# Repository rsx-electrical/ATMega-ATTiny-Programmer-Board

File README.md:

# ATMega ATTiny Programmer Board
UofT RSX's ATMega/ATTiny Programmer Board KiCad PCB designs for programming standalone ATMega328[tbd] and ATTiny[tbd] microcontrollers. Uses Arduino as programmer. By programming the microcontroller directly, custom boards can be smaller and cheaper.

## To-do
- 

## Repository Structure 
```
Programmer-Board/
├── ATMega/
│   └── ...
│
├── ATTiny/
│   └── ...
│
├── Programmer Board/
│   └── ...
│
├── guide.txt
└── README.md
```
## History/Patch Notes

### v1.0 - TBD
- Final Design Version 1

### v0.2 - TBD
- 

### v0.1 - Init
- General Project Struct Formed

## Materials
- Arduino Header
- Electrolytic Capacitor 10uF
- Decoupling Capacitors 100nF
- Resistor [1 - 10kΩ]
- ATMega328[tbd] or ATTiny[tbd] Socket

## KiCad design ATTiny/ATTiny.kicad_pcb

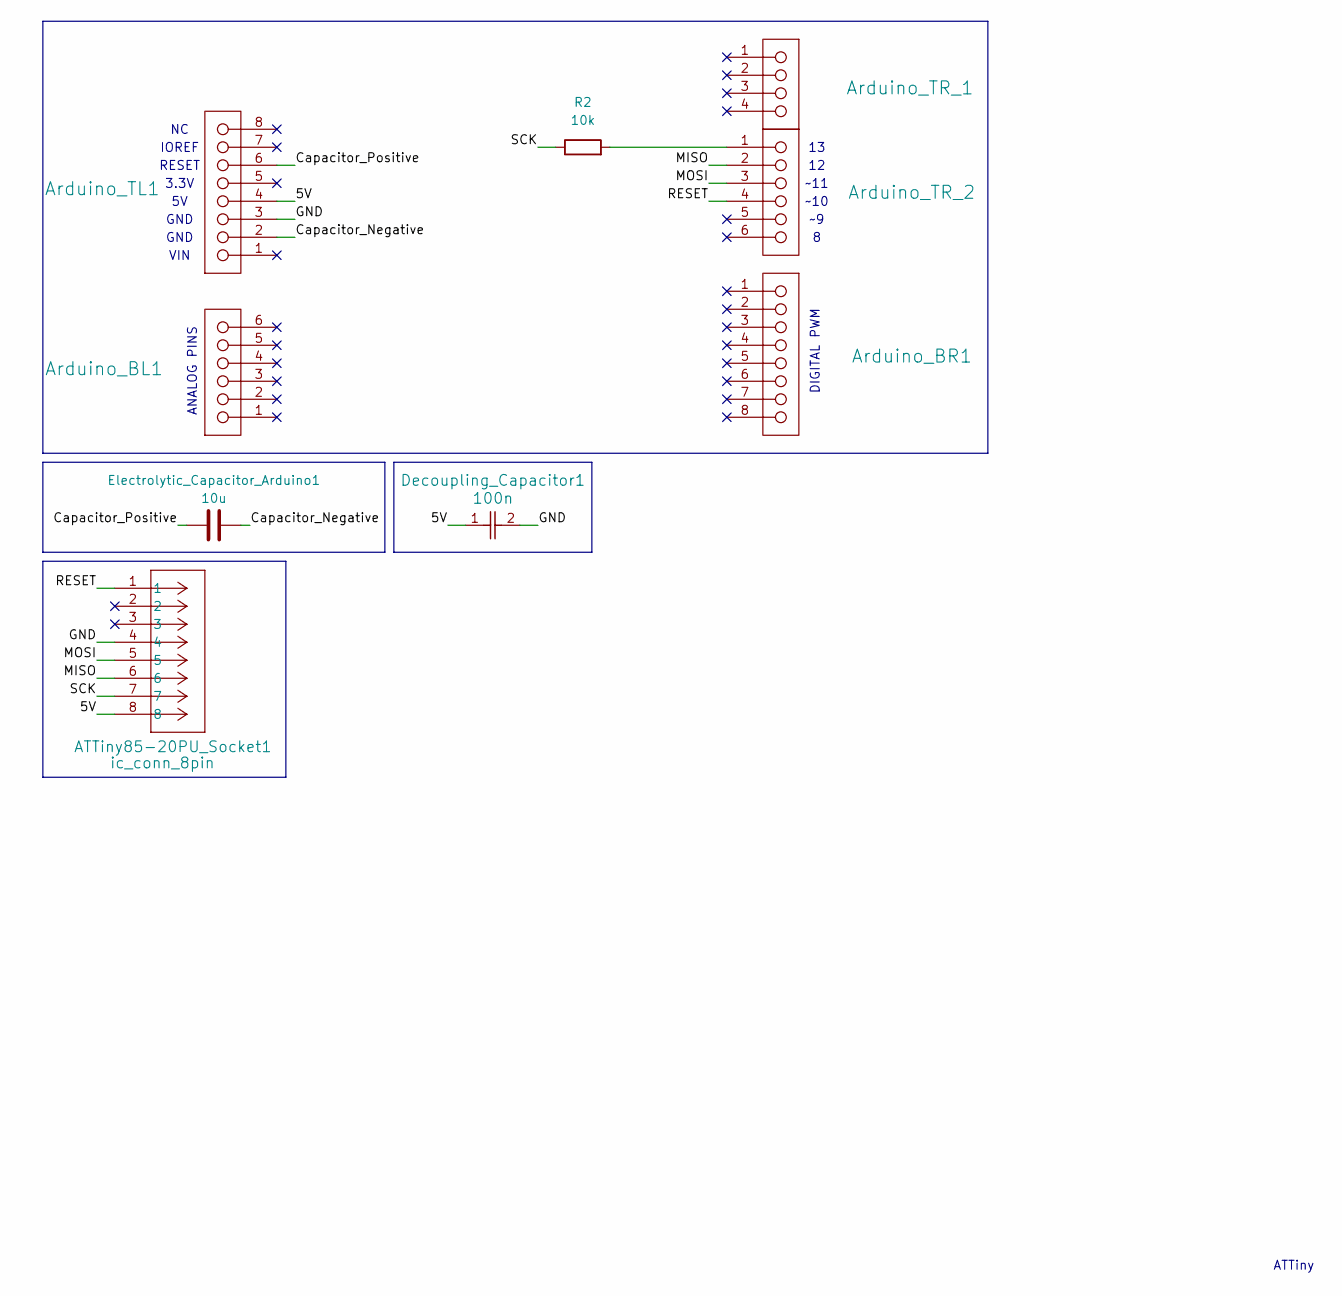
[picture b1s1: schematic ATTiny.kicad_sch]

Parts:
ATTiny85-20PU_Socket1: ic_conn_8pin; CONN8_1-2199298-2_TEC
Arduino_BL1: header_1x6_arduino; PinHeader_1x06_P2.54mm_Vertical; Working Voltage 250V; Withstanding Voltage 500V; Manufacturer Part Number 61000613321
Arduino_BR1: header_1x8_arduino; PinHeader_1x08_P2.54mm_Vertical; Working Voltage 250V; Withstanding Voltage 500V; Manufacturer Part Number 61000813321
Arduino_TL1: header_1x8_arduino; PinHeader_1x08_P2.54mm_Vertical; Working Voltage 250V; Withstanding Voltage 500V; Manufacturer Part Number 61000813321
Arduino_TR_1: header_1x4_arduino; PinHeader_1x04_P2.54mm_Vertical; Working Voltage 250V; Withstanding Voltage 500V; Manufacturer Part Number 61000411921
Arduino_TR_2: header_1x6_arduino; PinHeader_1x06_P2.54mm_Vertical; Working Voltage 250V; Withstanding Voltage 500V; Manufacturer Part Number 61000613321
Decoupling_Capacitor1: 100n; C_0603_1608Metric; MPN C0603C104K5RACTU
Electrolytic_Capacitor_Arduino1: 10u; C_0805_2012Metric; MPN GRM21BR61H106KE43L
R2: 10k; R_0603_1608Metric; MPN RMCF0603JT10K0

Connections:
/5V: ATTiny85-20PU_Socket1.8, Arduino_TL1.4, Decoupling_Capacitor1.1
/Capacitor_Negative: Arduino_TL1.2, Electrolytic_Capacitor_Arduino1.1
/Capacitor_Positive: Arduino_TL1.6, Electrolytic_Capacitor_Arduino1.2
/GND: ATTiny85-20PU_Socket1.4, Arduino_TL1.3, Decoupling_Capacitor1.2
/MISO: ATTiny85-20PU_Socket1.6, Arduino_TR_2.2
/MOSI: ATTiny85-20PU_Socket1.5, Arduino_TR_2.3
/RESET: ATTiny85-20PU_Socket1.1, Arduino_TR_2.4
/SCK: ATTiny85-20PU_Socket1.7, R2.1
unnamed: Arduino_TR_2.1, R2.2

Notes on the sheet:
GND
~10
IOREF
DIGITAL PWM
ANALOG PINS
ATTiny
RESET
3.3V
VIN
~11

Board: 2 copper layers, 9 parts (0 on the bottom side), 9 nets, no tracks yet.

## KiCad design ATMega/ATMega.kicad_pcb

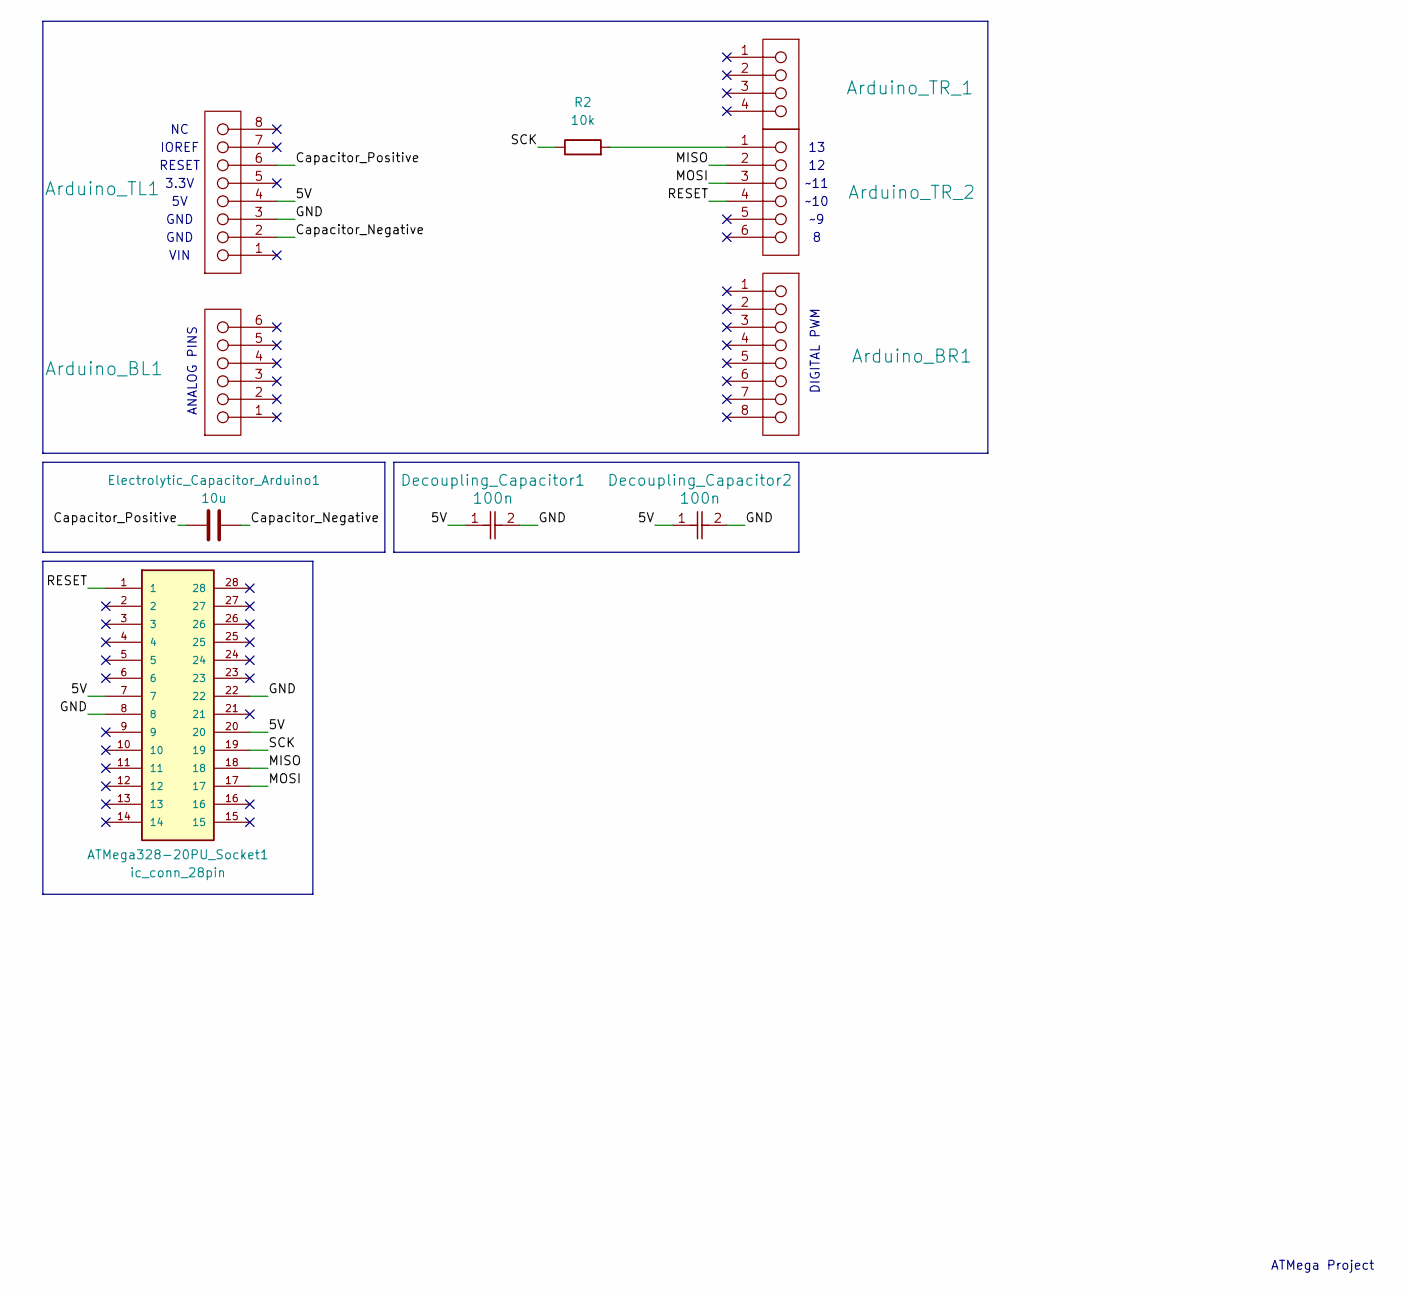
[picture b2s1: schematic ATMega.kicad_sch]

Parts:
ATMega328-20PU_Socket1: ic_conn_28pin; OST_ED281DT; PARTREV D
Arduino_BL1: header_1x6_arduino; PinHeader_1x06_P2.54mm_Vertical; Working Voltage 250V; Withstanding Voltage 500V; Manufacturer Part Number 61000613321
Arduino_BR1: header_1x8_arduino; PinHeader_1x08_P2.54mm_Vertical; Working Voltage 250V; Withstanding Voltage 500V; Manufacturer Part Number 61000813321
Arduino_TL1: header_1x8_arduino; PinHeader_1x08_P2.54mm_Vertical; Working Voltage 250V; Withstanding Voltage 500V; Manufacturer Part Number 61000813321
Arduino_TR_1: header_1x4_arduino; PinHeader_1x04_P2.54mm_Vertical; Working Voltage 250V; Withstanding Voltage 500V; Manufacturer Part Number 61000411921
Arduino_TR_2: header_1x6_arduino; PinHeader_1x06_P2.54mm_Vertical; Working Voltage 250V; Withstanding Voltage 500V; Manufacturer Part Number 61000613321
Decoupling_Capacitor1, Decoupling_Capacitor2: 100n; C_0603_1608Metric; MPN C0603C104K5RACTU
Electrolytic_Capacitor_Arduino1: 10u; C_0805_2012Metric; MPN GRM21BR61H106KE43L
R2: 10k; R_0603_1608Metric; MPN RMCF0603JT10K0

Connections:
/5V: ATMega328-20PU_Socket1.7, ATMega328-20PU_Socket1.20, Arduino_TL1.4, Decoupling_Capacitor1.1, Decoupling_Capacitor2.1
/Capacitor_Negative: Arduino_TL1.2, Electrolytic_Capacitor_Arduino1.1
/Capacitor_Positive: Arduino_TL1.6, Electrolytic_Capacitor_Arduino1.2
/GND: ATMega328-20PU_Socket1.8, ATMega328-20PU_Socket1.22, Arduino_TL1.3, Decoupling_Capacitor1.2, Decoupling_Capacitor2.2
/MISO: ATMega328-20PU_Socket1.18, Arduino_TR_2.2
/MOSI: ATMega328-20PU_Socket1.17, Arduino_TR_2.3
/RESET: ATMega328-20PU_Socket1.1, Arduino_TR_2.4
/SCK: ATMega328-20PU_Socket1.19, R2.1
unnamed: Arduino_TR_2.1, R2.2

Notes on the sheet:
ATMega Project
IOREF
ANALOG PINS
RESET
~10
GND
DIGITAL PWM
~11
3.3V
VIN

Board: 2 copper layers, 10 parts (0 on the bottom side), 9 nets, no tracks yet.

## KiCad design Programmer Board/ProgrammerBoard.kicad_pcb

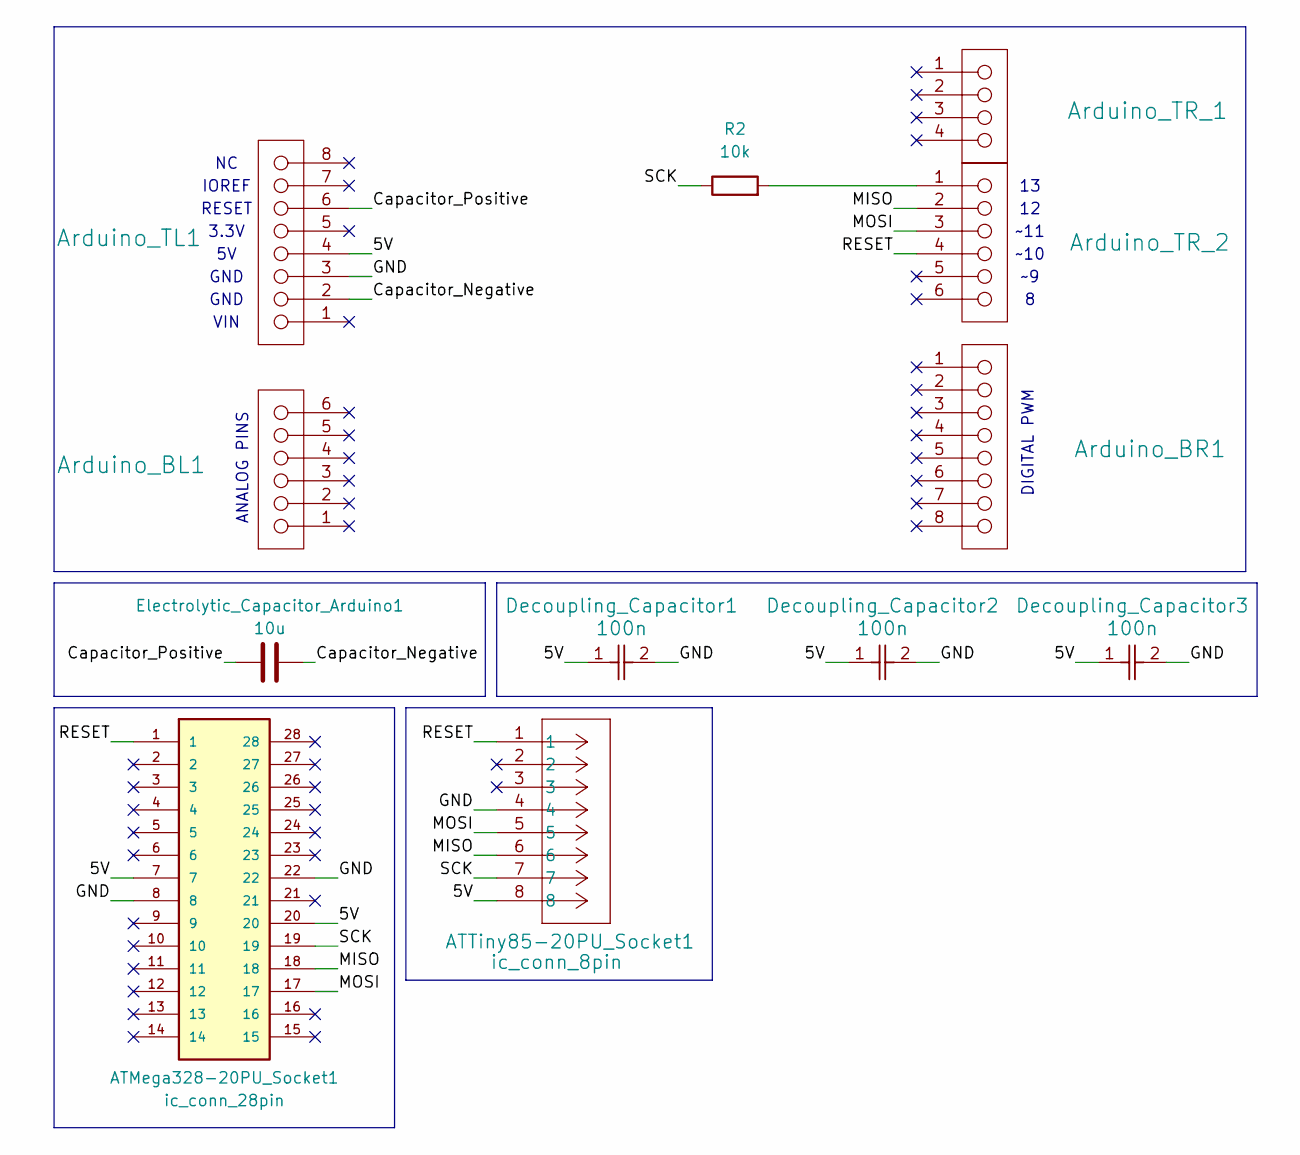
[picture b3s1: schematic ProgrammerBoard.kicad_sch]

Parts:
ATMega328-20PU_Socket1: ic_conn_28pin; OST_ED281DT; PARTREV D
ATTiny85-20PU_Socket1: ic_conn_8pin; CONN8_1-2199298-2_TEC
Arduino_BL1: header_1x6_arduino; PinHeader_1x06_P2.54mm_Vertical; Working Voltage 250V; Withstanding Voltage 500V; Manufacturer Part Number 61000613321
Arduino_BR1: header_1x8_arduino; PinHeader_1x08_P2.54mm_Vertical; Working Voltage 250V; Withstanding Voltage 500V; Manufacturer Part Number 61000813321
Arduino_TL1: header_1x8_arduino; PinHeader_1x08_P2.54mm_Vertical; Working Voltage 250V; Withstanding Voltage 500V; Manufacturer Part Number 61000813321
Arduino_TR_1: header_1x4_arduino; PinHeader_1x04_P2.54mm_Vertical; Working Voltage 250V; Withstanding Voltage 500V; Manufacturer Part Number 61000411921
Arduino_TR_2: header_1x6_arduino; PinHeader_1x06_P2.54mm_Vertical; Working Voltage 250V; Withstanding Voltage 500V; Manufacturer Part Number 61000613321
Decoupling_Capacitor1, Decoupling_Capacitor2, Decoupling_Capacitor3: 100n; C_0603_1608Metric; MPN C0603C104K5RACTU
Electrolytic_Capacitor_Arduino1: 10u; C_0805_2012Metric; MPN GRM21BR61H106KE43L
R2: 10k; R_0603_1608Metric; MPN RMCF0603JT10K0

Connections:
/5V: ATMega328-20PU_Socket1.7, ATMega328-20PU_Socket1.20, ATTiny85-20PU_Socket1.8, Arduino_TL1.4, Decoupling_Capacitor1.1, Decoupling_Capacitor2.1, Decoupling_Capacitor3.1
/Capacitor_Negative: Arduino_TL1.2, Electrolytic_Capacitor_Arduino1.1
/Capacitor_Positive: Arduino_TL1.6, Electrolytic_Capacitor_Arduino1.2
/GND: ATMega328-20PU_Socket1.8, ATMega328-20PU_Socket1.22, ATTiny85-20PU_Socket1.4, Arduino_TL1.3, Decoupling_Capacitor1.2, Decoupling_Capacitor2.2, Decoupling_Capacitor3.2
/MISO: ATMega328-20PU_Socket1.18, ATTiny85-20PU_Socket1.6, Arduino_TR_2.2
/MOSI: ATMega328-20PU_Socket1.17, ATTiny85-20PU_Socket1.5, Arduino_TR_2.3
/RESET: ATMega328-20PU_Socket1.1, ATTiny85-20PU_Socket1.1, Arduino_TR_2.4
/SCK: ATMega328-20PU_Socket1.19, ATTiny85-20PU_Socket1.7, R2.1
unnamed: Arduino_TR_2.1, R2.2

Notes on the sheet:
3.3V
~10
DIGITAL PWM
~11
ANALOG PINS
GND
IOREF
RESET
VIN

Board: 2 copper layers, 12 parts (0 on the bottom side), 9 nets, no tracks yet.
